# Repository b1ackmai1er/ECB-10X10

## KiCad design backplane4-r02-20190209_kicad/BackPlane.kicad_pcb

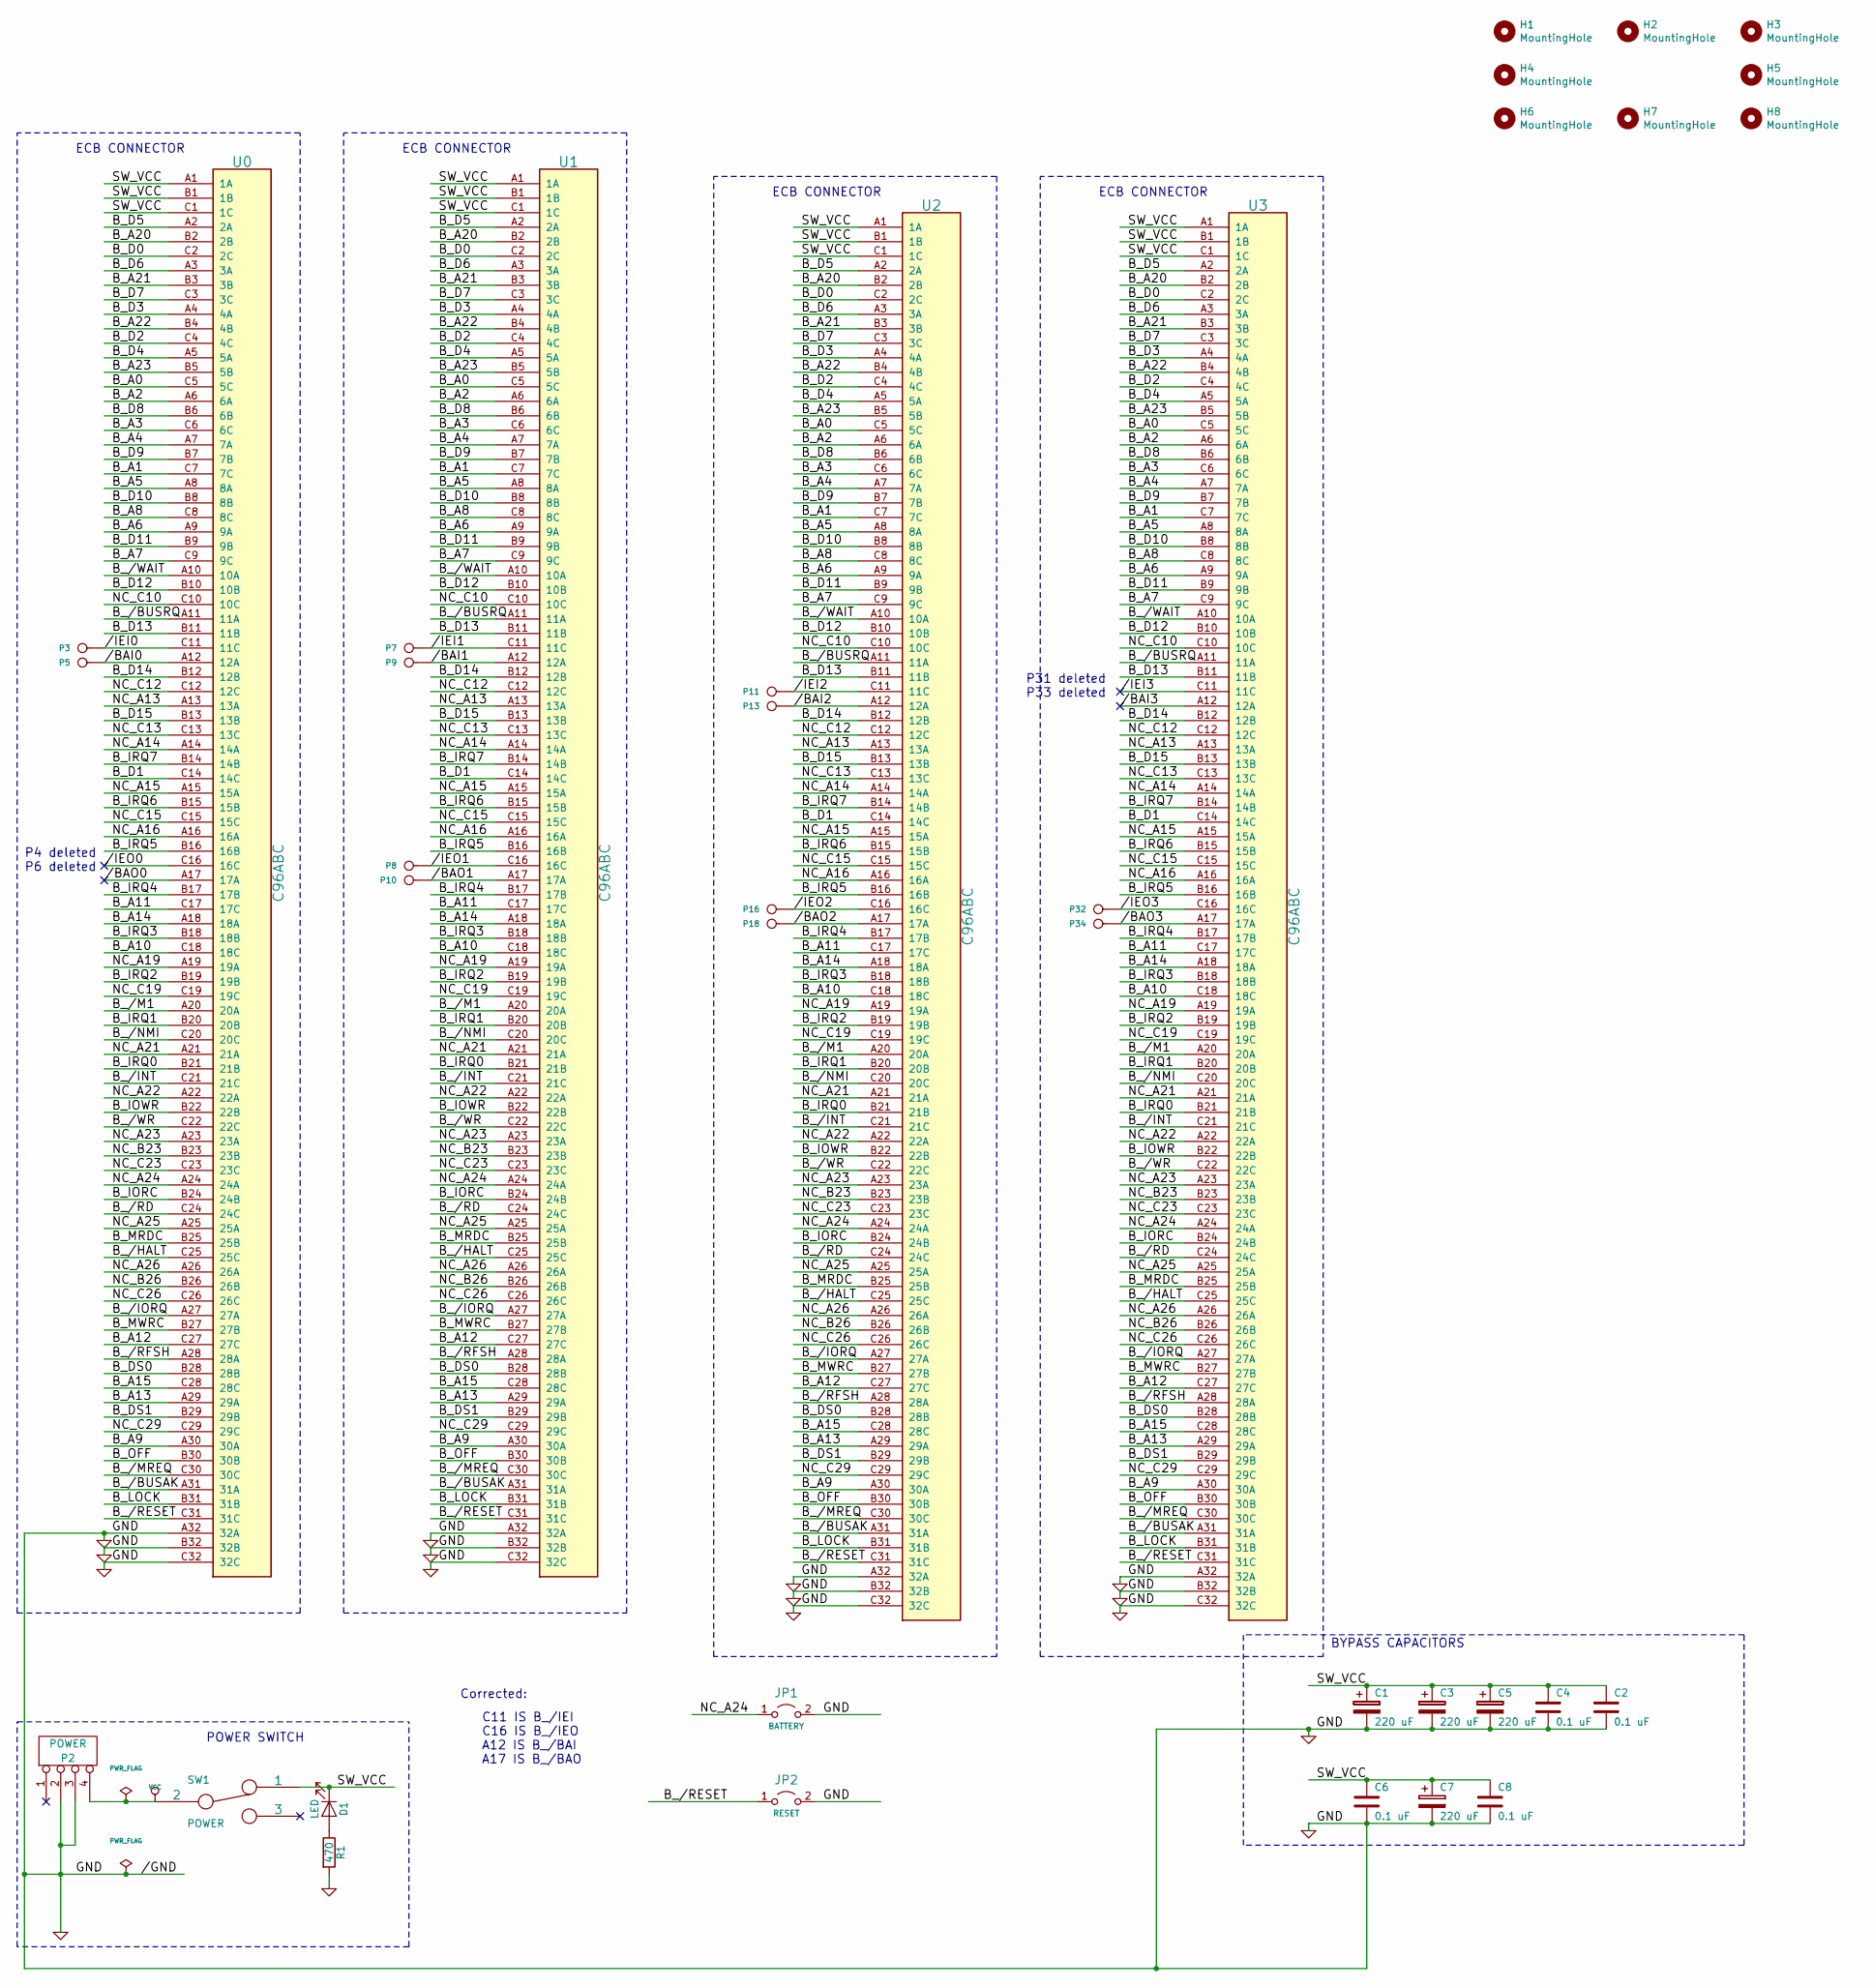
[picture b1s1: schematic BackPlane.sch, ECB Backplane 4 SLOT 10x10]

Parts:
C1, C3, C5, C7: 220 uF; CP_Radial_D8.0mm_P5.00mm
C2, C4, C6, C8: 0.1 uF; C_Disc_D7.0mm_W2.5mm_P5.00mm
D1: LED; LED_D5.0mm
H1, H2, H3, H4, H5, H6, H7, H8: MountingHole; MountingHole_3.2mm_M3
JP1: BATTERY; PinHeader_1x02_P2.54mm_Vertical
JP2: RESET; PinHeader_1x02_P2.54mm_Vertical
P2: POWER; bornier4
P3, P5, P7, P8, P9, P10, P11, P13, P16, P18, P32, P34: CONN_1; 0pin
R1: 470; R_Axial_DIN0204_L3.6mm_D1.6mm_P7.62mm_Horizontal
SW1: POWER; Switch-SPST-0.185
U0, U1, U2, U3: C96ABC; C96ABCFD-jrc

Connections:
//BAI0: P5.1, U0.A12 (12A)
//BAI1: P9.1, U1.A12 (12A)
//BAI2: P13.1, U2.A12 (12A)
//BAI3: U3.A12 (12A)
//BAO0: U0.A17 (17A)
//BAO1: P10.1, U1.A17 (17A)
//BAO2: P18.1, U2.A17 (17A)
//BAO3: P34.1, U3.A17 (17A)
//IEI0: P3.1, U0.C11 (11C)
//IEI1: P7.1, U1.C11 (11C)
//IEI2: P11.1, U2.C11 (11C)
//IEI3: U3.C11 (11C)
//IEO0: U0.C16 (16C)
//IEO1: P8.1, U1.C16 (16C)
//IEO2: P16.1, U2.C16 (16C)
//IEO3: P32.1, U3.C16 (16C)
/B_/BUSAK: U0.A31 (31A), U1.A31 (31A), U2.A31 (31A), U3.A31 (31A)
/B_/BUSRQ: U0.A11 (11A), U1.A11 (11A), U2.A11 (11A), U3.A11 (11A)
/B_/HALT: U0.C25 (25C), U1.C25 (25C), U2.C25 (25C), U3.C25 (25C)
/B_/INT: U0.C21 (21C), U1.C21 (21C), U2.C21 (21C), U3.C21 (21C)
/B_/IORQ: U0.A27 (27A), U1.A27 (27A), U2.A27 (27A), U3.A27 (27A)
/B_/M1: U0.A20 (20A), U1.A20 (20A), U2.A20 (20A), U3.A20 (20A)
/B_/MREQ: U0.C30 (30C), U1.C30 (30C), U2.C30 (30C), U3.C30 (30C)
/B_/NMI: U0.C20 (20C), U1.C20 (20C), U2.C20 (20C), U3.C20 (20C)
/B_/RD: U0.C24 (24C), U1.C24 (24C), U2.C24 (24C), U3.C24 (24C)
/B_/RESET: JP2.1 (A), U0.C31 (31C), U1.C31 (31C), U2.C31 (31C), U3.C31 (31C)
/B_/RFSH: U0.A28 (28A), U1.A28 (28A), U2.A28 (28A), U3.A28 (28A)
/B_/WAIT: U0.A10 (10A), U1.A10 (10A), U2.A10 (10A), U3.A10 (10A)
/B_/WR: U0.C22 (22C), U1.C22 (22C), U2.C22 (22C), U3.C22 (22C)
/B_A0: U0.C5 (5C), U1.C5 (5C), U2.C5 (5C), U3.C5 (5C)
/B_A1: U0.C7 (7C), U1.C7 (7C), U2.C7 (7C), U3.C7 (7C)
/B_A2: U0.A6 (6A), U1.A6 (6A), U2.A6 (6A), U3.A6 (6A)
/B_A3: U0.C6 (6C), U1.C6 (6C), U2.C6 (6C), U3.C6 (6C)
/B_A4: U0.A7 (7A), U1.A7 (7A), U2.A7 (7A), U3.A7 (7A)
/B_A5: U0.A8 (8A), U1.A8 (8A), U2.A8 (8A), U3.A8 (8A)
/B_A6: U0.A9 (9A), U1.A9 (9A), U2.A9 (9A), U3.A9 (9A)
/B_A7: U0.C9 (9C), U1.C9 (9C), U2.C9 (9C), U3.C9 (9C)
/B_A8: U0.C8 (8C), U1.C8 (8C), U2.C8 (8C), U3.C8 (8C)
/B_A9: U0.A30 (30A), U1.A30 (30A), U2.A30 (30A), U3.A30 (30A)
/B_A10: U0.C18 (18C), U1.C18 (18C), U2.C18 (18C), U3.C18 (18C)
/B_A11: U0.C17 (17C), U1.C17 (17C), U2.C17 (17C), U3.C17 (17C)
/B_A12: U0.C27 (27C), U1.C27 (27C), U2.C27 (27C), U3.C27 (27C)
/B_A13: U0.A29 (29A), U1.A29 (29A), U2.A29 (29A), U3.A29 (29A)
/B_A14: U0.A18 (18A), U1.A18 (18A), U2.A18 (18A), U3.A18 (18A)
/B_A15: U0.C28 (28C), U1.C28 (28C), U2.C28 (28C), U3.C28 (28C)
/B_A20: U0.B2 (2B), U1.B2 (2B), U2.B2 (2B), U3.B2 (2B)
/B_A21: U0.B3 (3B), U1.B3 (3B), U2.B3 (3B), U3.B3 (3B)
/B_A22: U0.B4 (4B), U1.B4 (4B), U2.B4 (4B), U3.B4 (4B)
/B_A23: U0.B5 (5B), U1.B5 (5B), U2.B5 (5B), U3.B5 (5B)
/B_D0: U0.C2 (2C), U1.C2 (2C), U2.C2 (2C), U3.C2 (2C)
/B_D1: U0.C14 (14C), U1.C14 (14C), U2.C14 (14C), U3.C14 (14C)
/B_D2: U0.C4 (4C), U1.C4 (4C), U2.C4 (4C), U3.C4 (4C)
/B_D3: U0.A4 (4A), U1.A4 (4A), U2.A4 (4A), U3.A4 (4A)
/B_D4: U0.A5 (5A), U1.A5 (5A), U2.A5 (5A), U3.A5 (5A)
/B_D5: U0.A2 (2A), U1.A2 (2A), U2.A2 (2A), U3.A2 (2A)
/B_D6: U0.A3 (3A), U1.A3 (3A), U2.A3 (3A), U3.A3 (3A)
/B_D7: U0.C3 (3C), U1.C3 (3C), U2.C3 (3C), U3.C3 (3C)
/B_D8: U0.B6 (6B), U1.B6 (6B), U2.B6 (6B), U3.B6 (6B)
/B_D9: U0.B7 (7B), U1.B7 (7B), U2.B7 (7B), U3.B7 (7B)
/B_D10: U0.B8 (8B), U1.B8 (8B), U2.B8 (8B), U3.B8 (8B)
/B_D11: U0.B9 (9B), U1.B9 (9B), U2.B9 (9B), U3.B9 (9B)
/B_D12: U0.B10 (10B), U1.B10 (10B), U2.B10 (10B), U3.B10 (10B)
/B_D13: U0.B11 (11B), U1.B11 (11B), U2.B11 (11B), U3.B11 (11B)
/B_D14: U0.B12 (12B), U1.B12 (12B), U2.B12 (12B), U3.B12 (12B)
/B_D15: U0.B13 (13B), U1.B13 (13B), U2.B13 (13B), U3.B13 (13B)
/B_DS0: U0.B28 (28B), U1.B28 (28B), U2.B28 (28B), U3.B28 (28B)
/B_DS1: U0.B29 (29B), U1.B29 (29B), U2.B29 (29B), U3.B29 (29B)
/B_IORC: U0.B24 (24B), U1.B24 (24B), U2.B24 (24B), U3.B24 (24B)
/B_IOWR: U0.B22 (22B), U1.B22 (22B), U2.B22 (22B), U3.B22 (22B)
/B_IRQ0: U0.B21 (21B), U1.B21 (21B), U2.B21 (21B), U3.B21 (21B)
/B_IRQ1: U0.B20 (20B), U1.B20 (20B), U2.B20 (20B), U3.B20 (20B)
/B_IRQ2: U0.B19 (19B), U1.B19 (19B), U2.B19 (19B), U3.B19 (19B)
/B_IRQ3: U0.B18 (18B), U1.B18 (18B), U2.B18 (18B), U3.B18 (18B)
/B_IRQ4: U0.B17 (17B), U1.B17 (17B), U2.B17 (17B), U3.B17 (17B)
/B_IRQ5: U0.B16 (16B), U1.B16 (16B), U2.B16 (16B), U3.B16 (16B)
/B_IRQ6: U0.B15 (15B), U1.B15 (15B), U2.B15 (15B), U3.B15 (15B)
/B_IRQ7: U0.B14 (14B), U1.B14 (14B), U2.B14 (14B), U3.B14 (14B)
/B_LOCK: U0.B31 (31B), U1.B31 (31B), U2.B31 (31B), U3.B31 (31B)
/B_MRDC: U0.B25 (25B), U1.B25 (25B), U2.B25 (25B), U3.B25 (25B)
/B_MWRC: U0.B27 (27B), U1.B27 (27B), U2.B27 (27B), U3.B27 (27B)
/B_OFF: U0.B30 (30B), U1.B30 (30B), U2.B30 (30B), U3.B30 (30B)
/NC_A13: U0.A13 (13A), U1.A13 (13A), U2.A13 (13A), U3.A13 (13A)
/NC_A14: U0.A14 (14A), U1.A14 (14A), U2.A14 (14A), U3.A14 (14A)
/NC_A15: U0.A15 (15A), U1.A15 (15A), U2.A15 (15A), U3.A15 (15A)
/NC_A16: U0.A16 (16A), U1.A16 (16A), U2.A16 (16A), U3.A16 (16A)
/NC_A19: U0.A19 (19A), U1.A19 (19A), U2.A19 (19A), U3.A19 (19A)
/NC_A21: U0.A21 (21A), U1.A21 (21A), U2.A21 (21A), U3.A21 (21A)
/NC_A22: U0.A22 (22A), U1.A22 (22A), U2.A22 (22A), U3.A22 (22A)
/NC_A23: U0.A23 (23A), U1.A23 (23A), U2.A23 (23A), U3.A23 (23A)
/NC_A24: JP1.1 (A), U0.A24 (24A), U1.A24 (24A), U2.A24 (24A), U3.A24 (24A)
/NC_A25: U0.A25 (25A), U1.A25 (25A), U2.A25 (25A), U3.A25 (25A)
/NC_A26: U0.A26 (26A), U1.A26 (26A), U2.A26 (26A), U3.A26 (26A)
/NC_B23: U0.B23 (23B), U1.B23 (23B), U2.B23 (23B), U3.B23 (23B)
/NC_B26: U0.B26 (26B), U1.B26 (26B), U2.B26 (26B), U3.B26 (26B)
/NC_C10: U0.C10 (10C), U1.C10 (10C), U2.C10 (10C), U3.C10 (10C)
/NC_C12: U0.C12 (12C), U1.C12 (12C), U2.C12 (12C), U3.C12 (12C)
/NC_C13: U0.C13 (13C), U1.C13 (13C), U2.C13 (13C), U3.C13 (13C)
/NC_C15: U0.C15 (15C), U1.C15 (15C), U2.C15 (15C), U3.C15 (15C)
/NC_C19: U0.C19 (19C), U1.C19 (19C), U2.C19 (19C), U3.C19 (19C)
/NC_C23: U0.C23 (23C), U1.C23 (23C), U2.C23 (23C), U3.C23 (23C)
/NC_C26: U0.C26 (26C), U1.C26 (26C), U2.C26 (26C), U3.C26 (26C)
/NC_C29: U0.C29 (29C), U1.C29 (29C), U2.C29 (29C), U3.C29 (29C)
/SW_VCC: C1.1, C2.1, C3.1, C4.1, C5.1, C6.1, C7.1, C8.1, D1.1 (K), SW1.1, U0.A1 (1A), U0.B1 (1B), U0.C1 (1C), U1.A1 (1A), U1.B1 (1B), U1.C1 (1C), U2.A1 (1A), U2.B1 (1B), U2.C1 (1C), U3.A1 (1A), U3.B1 (1B), U3.C1 (1C)
GND: C1.2, C2.2, C3.2, C4.2, C5.2, C6.2, C7.2, C8.2, JP1.2 (B), JP2.2 (B), P2.2, P2.3, R1.2, U0.A32 (32A), U0.B32 (32B), U0.C32 (32C), U1.A32 (32A), U1.B32 (32B), U1.C32 (32C), U2.A32 (32A), U2.B32 (32B), U2.C32 (32C), U3.A32 (32A), U3.B32 (32B), U3.C32 (32C)
unnamed: D1.2 (A), R1.1
VCC: P2.4, SW1.2

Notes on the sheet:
P31 deleted P33 deleted
P4 deleted P6 deleted
Corrected:
ECB CONNECTOR
C11 IS B_/IEI C16 IS B_/IEO A12 IS B_/BAI A17 IS B_/BAO
BYPASS CAPACITORS
POWER SWITCH

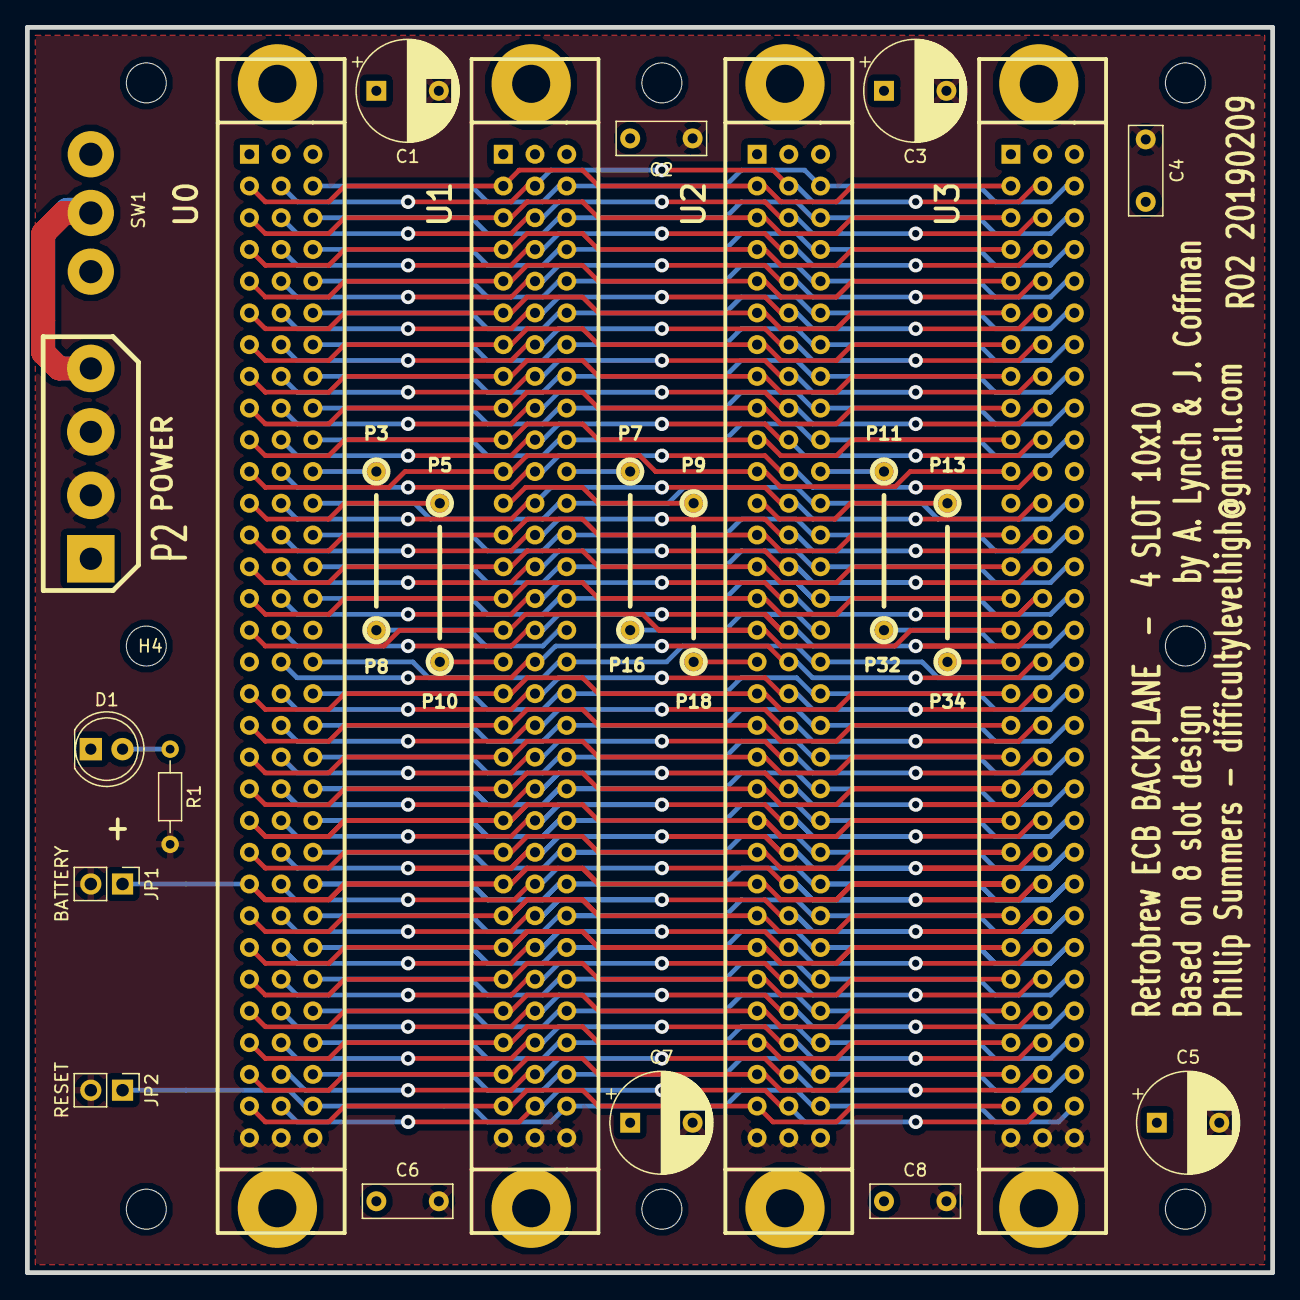
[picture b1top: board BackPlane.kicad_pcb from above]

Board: 2 copper layers, 99.7 x 99.7 mm, 38 parts (0 on the bottom side), 102 nets.
